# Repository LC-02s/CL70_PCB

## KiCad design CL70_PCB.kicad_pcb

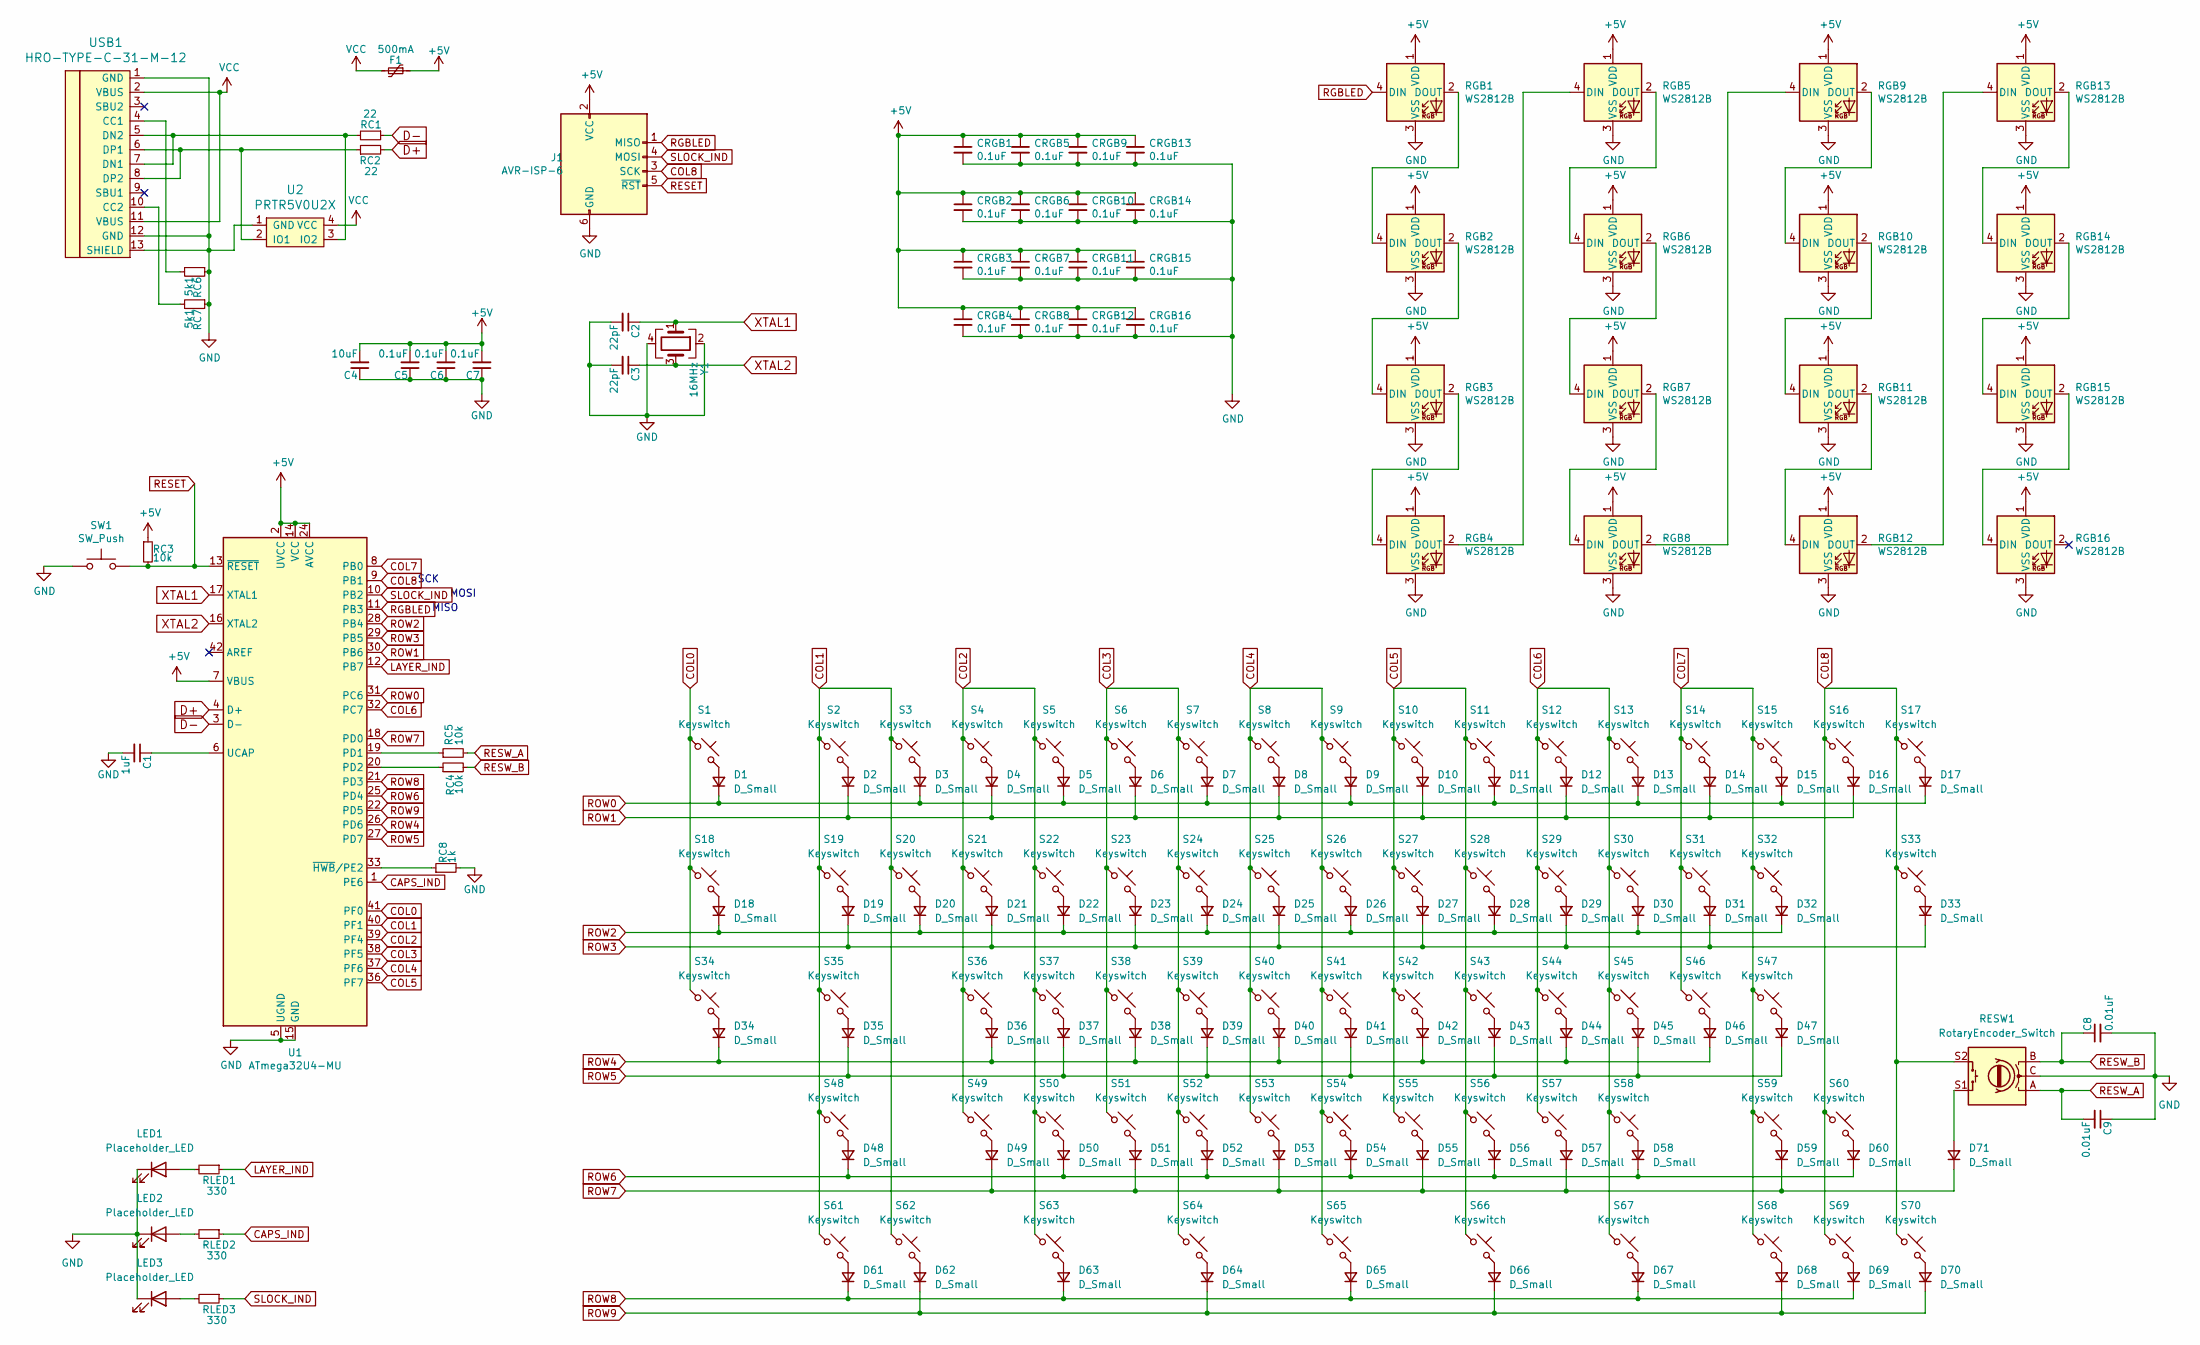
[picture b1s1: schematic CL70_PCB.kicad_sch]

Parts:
C1: 1uF; C_0603
C2, C3: 22pF; C_0603
C4: 10uF; C_0603
C5, C6, C7: 0.1uF; C_0603
C8, C9: 0.01uF; C_0603
CRGB1, CRGB2, CRGB3, CRGB4, CRGB5, CRGB6, CRGB7, CRGB8, CRGB9, CRGB10, CRGB11, CRGB12, CRGB13, CRGB14, CRGB15, CRGB16: 0.1uF; C_0603
D1, D2, D3, D4, D5, D6, D7, D8, D9, D10, D11, D12, D13, D14, D15, D16, D17, D18, D19, D20, D21, D22, D23, D24, D25, D26, D27, D28, D29, D30, D31, D32, D33, D34, D35, D36, D37, D38, D39, D40, D41, D42, D43, D44, D45, D46, D47, D48, D49, D50, D51, D52, D53, D54, D55, D56, D57, D58, D59, D60, D61, D62, D63, D64, D65, D66, D67, D68, D69, D70, D71: D_Small; D_SOD-123
F1: 500mA; Fuse_1206_3216Metric
J1: AVR-ISP-6; Reset_Pretty-Mask
LED1, LED2, LED3: Placeholder_LED; LED_D3.0mm-Pretty
RC1, RC2: 22; R_0603
RC3, RC4, RC5: 10k; R_0603
RC6, RC7: 5k1; R_0603
RC8: 1k; R_0603
RESW1: RotaryEncoder_Switch; RotaryEncoder_Alps_EC11E-Switch_Vertical_H20mm
RGB1, RGB2, RGB3, RGB4, RGB5, RGB6, RGB7, RGB8, RGB9, RGB10, RGB11, RGB12, RGB13, RGB14, RGB15, RGB16: WS2812B; LED_WS2812B-PLCC4
RLED1, RLED2, RLED3: 330; R_0603
S1, S2, S3, S4, S5, S6, S7, S8, S9, S10, S11, S12, S13, S14, S15, S16, S17, S18, S20, S21, S22, S23, S24, S25, S26, S27, S28, S29, S30, S31, S33, S34, S36, S37, S38, S39, S40, S41, S42, S43, S44, S45, S46, S49, S50, S51, S52, S53, S54, S55, S56, S57, S58, S60, S68, S69, S70: Keyswitch; MX_PCB_1.00u
S19, S32, S63, S66: Keyswitch; MX_PCB_1.50u
S35: Keyswitch; MX_PCB_1.75u
S47, S48: Keyswitch; Hotswap_MX_2.25u
S59: Keyswitch; Hotswap_MX_2.00u
S61, S62, S67: Keyswitch; MX_PCB_1.25u
S64, S65: Keyswitch; Hotswap_MX_3.00u
SW1: SW_Push; SKQG-1155865
U1: ATmega32U4-MU; QFN-44-1EP_7x7mm_Pitch0.5mm
U2: PRTR5V0U2X; SOT143B
USB1: HRO-TYPE-C-31-M-12; HRO-TYPE-C-31-M-12-Assembly
Y1: 16MHz; Crystal_SMD_3225-4Pin_3.2x2.5mm

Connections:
+5V: C4.2, C5.2, C6.2, C7.2, CRGB1.1, CRGB2.1, CRGB3.1, CRGB4.1, CRGB5.1, CRGB6.1, CRGB7.1, CRGB8.1, CRGB9.1, CRGB10.1, CRGB11.1, CRGB12.1, CRGB13.1, CRGB14.1, CRGB15.1, CRGB16.1, F1.1, J1.2 (VCC), RC3.1, RGB1.1 (VDD), RGB2.1 (VDD), RGB3.1 (VDD), RGB4.1 (VDD), RGB5.1 (VDD), RGB6.1 (VDD), RGB7.1 (VDD), RGB8.1 (VDD), RGB9.1 (VDD), RGB10.1 (VDD), RGB11.1 (VDD), RGB12.1 (VDD), RGB13.1 (VDD), RGB14.1 (VDD), RGB15.1 (VDD), RGB16.1 (VDD), U1.2 (UVCC), U1.7 (VBUS), U1.14 (VCC), U1.24 (AVCC), U1.34 (VCC), U1.44 (AVCC)
CAPS_IND: RLED2.1, U1.1 (PE6)
COL0: S1.1, S18.1, S34.1, U1.41 (PF0)
COL1: S2.1, S3.1, S19.1, S20.1, S35.1, S48.1, S61.1, S62.1, U1.40 (PF1)
COL2: S4.1, S5.1, S21.1, S22.1, S36.1, S37.1, S49.1, S50.1, S63.1, U1.39 (PF4)
COL3: S6.1, S7.1, S23.1, S24.1, S38.1, S39.1, S51.1, S52.1, S64.1, U1.38 (PF5)
COL4: S8.1, S9.1, S25.1, S26.1, S40.1, S41.1, S53.1, S54.1, S65.1, U1.37 (PF6)
COL5: S10.1, S11.1, S27.1, S28.1, S42.1, S43.1, S55.1, S56.1, S66.1, U1.36 (PF7)
COL6: S12.1, S13.1, S29.1, S30.1, S44.1, S45.1, S57.1, S58.1, S67.1, U1.32 (PC7)
COL7: S14.1, S15.1, S31.1, S32.1, S46.1, S47.1, S59.1, S68.1, U1.8 (PB0)
COL8: J1.3 (SCK), RESW1.S2, S16.1, S17.1, S33.1, S60.1, S69.1, S70.1, U1.9 (PB1)
D+: RC2.2, U1.4 (D+)
D-: RC1.1, U1.3 (D-)
GND: C1.2, C2.2, C3.2, C4.1, C5.1, C6.1, C7.1, C8.2, C9.1, CRGB1.2, CRGB2.2, CRGB3.2, CRGB4.2, CRGB5.2, CRGB6.2, CRGB7.2, CRGB8.2, CRGB9.2, CRGB10.2, CRGB11.2, CRGB12.2, CRGB13.2, CRGB14.2, CRGB15.2, CRGB16.2, J1.6 (GND), LED1.1 (K), LED2.1 (K), LED3.1 (K), RC6.1, RC7.1, RC8.2, RESW1.C, RGB1.3 (VSS), RGB2.3 (VSS), RGB3.3 (VSS), RGB4.3 (VSS), RGB5.3 (VSS), RGB6.3 (VSS), RGB7.3 (VSS), RGB8.3 (VSS), RGB9.3 (VSS), RGB10.3 (VSS), RGB11.3 (VSS), RGB12.3 (VSS), RGB13.3 (VSS), RGB14.3 (VSS), RGB15.3 (VSS), RGB16.3 (VSS), SW1.1, U1.5 (UGND), U1.15 (GND), U1.23 (GND), U1.35 (GND), U1.43 (GND), U1.45 (GND), U2.1 (GND), USB1.1 (GND), USB1.12 (GND), USB1.13 (SHIELD), Y1.2, Y1.4
LAYER_IND: RLED1.1, U1.12 (PB7)
unnamed: D1.2 (A), S1.2
unnamed: D2.2 (A), S2.2
unnamed: D3.2 (A), S3.2
unnamed: D4.2 (A), S4.2
unnamed: D5.2 (A), S5.2
unnamed: D6.2 (A), S6.2
unnamed: D7.2 (A), S7.2
unnamed: D8.2 (A), S8.2
unnamed: D9.2 (A), S9.2
unnamed: D10.2 (A), S10.2
unnamed: D11.2 (A), S11.2
unnamed: D12.2 (A), S12.2
unnamed: D13.2 (A), S13.2
unnamed: D14.2 (A), S14.2
unnamed: D15.2 (A), S15.2
unnamed: D16.2 (A), S16.2
unnamed: D17.2 (A), S17.2
unnamed: D18.2 (A), S18.2
unnamed: D19.2 (A), S19.2
unnamed: D20.2 (A), S20.2
unnamed: D21.2 (A), S21.2
unnamed: D22.2 (A), S22.2
unnamed: D23.2 (A), S23.2
unnamed: D24.2 (A), S24.2
unnamed: D25.2 (A), S25.2
unnamed: D26.2 (A), S26.2
unnamed: D27.2 (A), S27.2
unnamed: D28.2 (A), S28.2
unnamed: D29.2 (A), S29.2
unnamed: D30.2 (A), S30.2
unnamed: D31.2 (A), S31.2
unnamed: D32.2 (A), S32.2
unnamed: D33.2 (A), S33.2
unnamed: D34.2 (A), S34.2
unnamed: D35.2 (A), S35.2
unnamed: D36.2 (A), S36.2
unnamed: D37.2 (A), S37.2
unnamed: D38.2 (A), S38.2
unnamed: D39.2 (A), S39.2
unnamed: D40.2 (A), S40.2
unnamed: D41.2 (A), S41.2
unnamed: D42.2 (A), S42.2
unnamed: D43.2 (A), S43.2
unnamed: D44.2 (A), S44.2
unnamed: D45.2 (A), S45.2
unnamed: D46.2 (A), S46.2
unnamed: D47.2 (A), S47.2
unnamed: D48.2 (A), S48.2
unnamed: D49.2 (A), S49.2
unnamed: D50.2 (A), S50.2
unnamed: D51.2 (A), S51.2
unnamed: D52.2 (A), S52.2
unnamed: D53.2 (A), S53.2
unnamed: D54.2 (A), S54.2
unnamed: D55.2 (A), S55.2
unnamed: D56.2 (A), S56.2
unnamed: D57.2 (A), S57.2
unnamed: D58.2 (A), S58.2
unnamed: D59.2 (A), S59.2
unnamed: D60.2 (A), S60.2
unnamed: D61.2 (A), S61.2
unnamed: D62.2 (A), S62.2
unnamed: D63.2 (A), S63.2
unnamed: D64.2 (A), S64.2
unnamed: D65.2 (A), S65.2
unnamed: D66.2 (A), S66.2
unnamed: D67.2 (A), S67.2
unnamed: D68.2 (A), S68.2
unnamed: D69.2 (A), S69.2
unnamed: D70.2 (A), S70.2
unnamed: D71.2 (A), RESW1.S1
unnamed: LED1.2 (A), RLED1.2
unnamed: LED2.2 (A), RLED2.2
unnamed: LED3.2 (A), RLED3.2
unnamed: RGB1.2 (DOUT), RGB2.4 (DIN)
unnamed: RGB2.2 (DOUT), RGB3.4 (DIN)
unnamed: RGB3.2 (DOUT), RGB4.4 (DIN)
unnamed: RGB4.2 (DOUT), RGB5.4 (DIN)
unnamed: RGB5.2 (DOUT), RGB6.4 (DIN)
unnamed: RGB6.2 (DOUT), RGB7.4 (DIN)
unnamed: RGB7.2 (DOUT), RGB8.4 (DIN)
unnamed: RGB8.2 (DOUT), RGB9.4 (DIN)
unnamed: RGB9.2 (DOUT), RGB10.4 (DIN)
unnamed: RGB10.2 (DOUT), RGB11.4 (DIN)
unnamed: RGB11.2 (DOUT), RGB12.4 (DIN)
unnamed: RGB12.2 (DOUT), RGB13.4 (DIN)
unnamed: RGB13.2 (DOUT), RGB14.4 (DIN)
unnamed: RGB14.2 (DOUT), RGB15.4 (DIN)
unnamed: RGB15.2 (DOUT), RGB16.4 (DIN)
unnamed: RC5.1, U1.19 (PD1)
unnamed: RC4.1, U1.20 (PD2)
unnamed: C1.1, U1.6 (UCAP)
unnamed: RC8.1, U1.33 (~HWB/PE2)
unnamed: RC2.1, U2.2 (IO1), USB1.6 (DP1), USB1.8 (DP2)
unnamed: RC1.2, U2.3 (IO2), USB1.5 (DN2), USB1.7 (DN1)
unnamed: RC6.2, USB1.4 (CC1)
unnamed: RC7.2, USB1.10 (CC2)
RESET: J1.5 (~RST), RC3.2, SW1.2, U1.13 (~RESET)
RESW_A: C9.2, RC5.2, RESW1.A
RESW_B: C8.1, RC4.2, RESW1.B
RGBLED: J1.1 (MISO), RGB1.4 (DIN), U1.11 (PB3)
ROW0: D1.1 (K), D3.1 (K), D5.1 (K), D7.1 (K), D9.1 (K), D11.1 (K), D13.1 (K), D15.1 (K), D17.1 (K), U1.31 (PC6)
ROW1: D2.1 (K), D4.1 (K), D6.1 (K), D8.1 (K), D10.1 (K), D12.1 (K), D14.1 (K), D16.1 (K), U1.30 (PB6)
ROW2: D18.1 (K), D20.1 (K), D22.1 (K), D24.1 (K), D26.1 (K), D28.1 (K), D30.1 (K), D32.1 (K), U1.28 (PB4)
ROW3: D19.1 (K), D21.1 (K), D23.1 (K), D25.1 (K), D27.1 (K), D29.1 (K), D31.1 (K), D33.1 (K), U1.29 (PB5)
ROW4: D34.1 (K), D36.1 (K), D38.1 (K), D40.1 (K), D42.1 (K), D44.1 (K), D46.1 (K), U1.26 (PD6)
ROW5: D35.1 (K), D37.1 (K), D39.1 (K), D41.1 (K), D43.1 (K), D45.1 (K), D47.1 (K), U1.27 (PD7)
ROW6: D48.1 (K), D50.1 (K), D52.1 (K), D54.1 (K), D56.1 (K), D58.1 (K), D60.1 (K), U1.25 (PD4)
ROW7: D49.1 (K), D51.1 (K), D53.1 (K), D55.1 (K), D57.1 (K), D59.1 (K), D71.1 (K), U1.18 (PD0)
ROW8: D61.1 (K), D63.1 (K), D65.1 (K), D67.1 (K), D69.1 (K), U1.21 (PD3)
ROW9: D62.1 (K), D64.1 (K), D66.1 (K), D68.1 (K), D70.1 (K), U1.22 (PD5)
SLOCK_IND: J1.4 (MOSI), RLED3.1, U1.10 (PB2)
VCC: F1.2, U2.4 (VCC), USB1.2 (VBUS), USB1.11 (VBUS)
XTAL1: C2.1, U1.17 (XTAL1), Y1.1
XTAL2: C3.1, U1.16 (XTAL2), Y1.3

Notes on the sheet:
SCK
MISO
MOSI

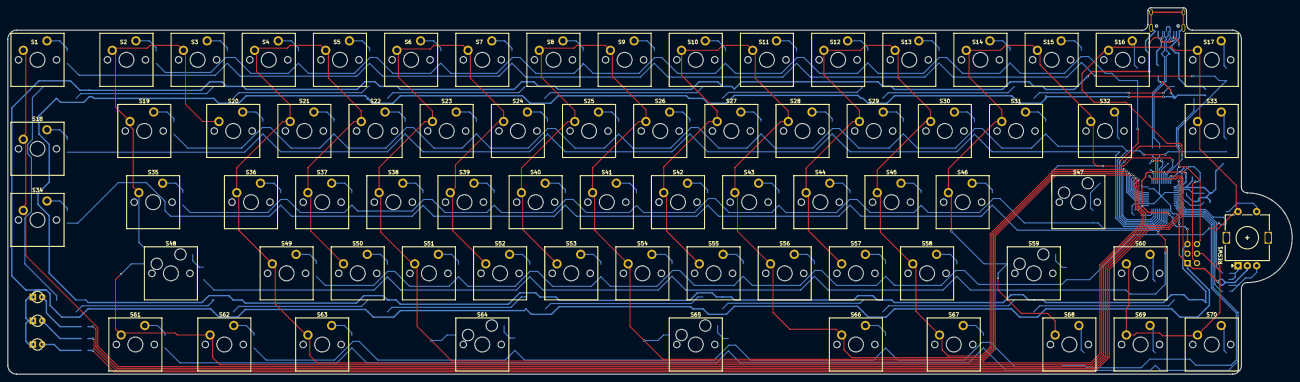
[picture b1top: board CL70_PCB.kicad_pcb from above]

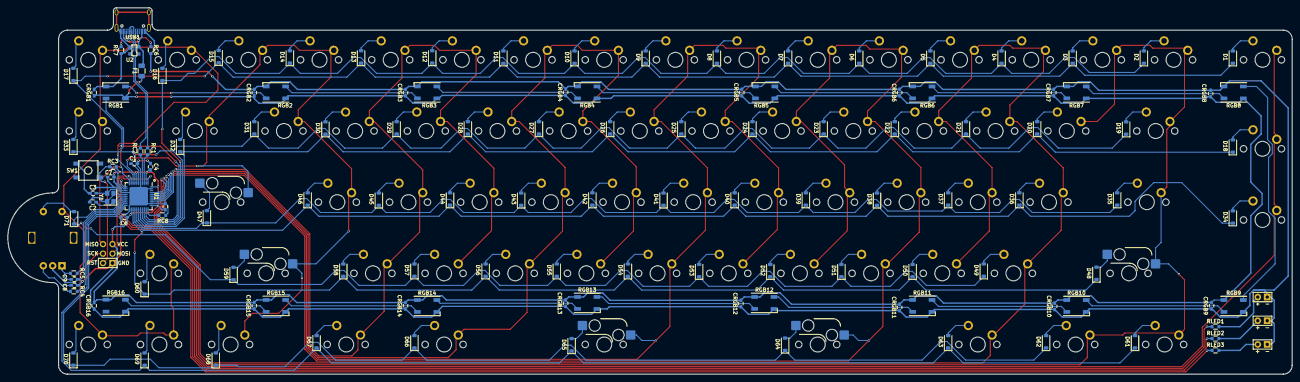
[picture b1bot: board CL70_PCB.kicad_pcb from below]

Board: 2 copper layers, 343.8 x 98.1 mm, 204 parts (130 on the bottom side), 130 nets.

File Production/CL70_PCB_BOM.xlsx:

Component | Description | Part | References | Value | Footprint | Quantity Per PCB
1.0 | Capacitor, Ceramic, 0603, ≥15V | C_Small | C1 | 1uF | C_0603 | 1.0
2.0 | Capacitor, Ceramic, 0603, ≥15V | C_Small | C2, C3 | 22pF | C_0603 | 2.0
3.0 | Capacitor, Ceramic, 0603, ≥15V | C_Small | C5, C6, C7, CRGB1, CRGB2, CRGB3, CRGB4, CRGB5, CRGB6, CRGB7, CRGB8, CRGB9, CRGB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 | 0.1uF | C_0603 | 19.0
4.0 | Capacitor, Ceramic, 0603, ≥15V | C_Small | C8, C9 | 0.01uF | C_0603 | 2.0
5.0 | Diode, Generic, SOD-123 | D_Small | D1, D2, D3, D4, D5, D6, D7, D8, D9, D10, D11, D12, D13, D14, D15, D16, D17, D18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 | SOD-323 | D_SOD-123 | 71.0
6.0 | Polyfuse, 1206, 500mA Hold, 1A Trip, ≥15V | Polyfuse_Small | F1 | 500mA | Fuse_SMD1206_Wave | 1.0
7.0 | Resistor, Generic, 0603 | R_Small | RC1, RC2 | 22.0 | R_0603 | 2.0
8.0 | Resistor, Generic, 0603 | R_Small | RC3, RC4, RC5 | 10k | R_0603 | 3.0
9.0 | Resistor, Generic, 0603 | R_Small | RC6, RC7 | 5k1 | R_0603 | 2.0
10.0 | Resistor, Generic, 0603 | R_Small | RC8 | 1k | R_0603 | 1.0
11.0 | Resistor, Generic, 0603 | R_Small | RLED1, RLED2, RLED3 | 330.0 | R_0603 | 3.0
12.0 | RGB LED, WS2812B, 5050 | WS2812B | RGB1, RGB2, RGB3, RGB4, RGB5, RGB6, RGB7, RGB8, RGB9, RGB10, RGB11, RGB12, RGB1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 | WS2812B | LED_WS2812B-PLCC4 | 16.0
13.0 | Push button, 5.2 x 5.2mm | SW_Push | SW1 | SW_Push | SKQG-1155865 | 1.0
14.0 | ATmega32U4-MU | ATmega32U4-MU | U1 | ATmega32U4-MU | QFN-44-1EP_7x7mm_Pitch0.5mm | 1.0
15.0 | ESD Protection IC, PRTR5V0U2X,215 | PRTR5V0U2X | U2 | PRTR5V0U2X | SOT143B | 1.0
16.0 | USB Type-C Connector, HRO TYPE-C-31-M-12 | HRO-TYPE-C-31-M-12 | USB1 | HRO-TYPE-C-31-M-12 | HRO-TYPE-C-31-M-12-Assembly | 1.0
17.0 | Crystal, 3.2 x 2.5mm, 16MHz | Crystal_GND24 | Y1 | 16MHz | Crystal_SMD_3225-4pin_3.2x2.5mm | 1.0
Component Groups: | 17.0
Component Count: | 128.0
Fitted Components: | 128.0
Number of PCBs: | 1.0
Total components: | 128.0
Schematic Version:
Schematic Date:
BoM Date: | 45869.0
Schematic Source:
KiCad Version: | Eeschema (9.0.2)-1

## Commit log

2025-07-26 Add wiring
2025-08-01 Add production files
2025-08-09 Update PCB Outline
